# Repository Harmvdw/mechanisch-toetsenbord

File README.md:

# Mechanisch toetsenbord (metaal, split, Lily58-geïnspireerd)

Doel: een split keyboard met aluminium behuizing en plaat, zelf ontworpen in Fusion 360 en zelf gefreesd. Inspiratiebron is de Lily58 (58 toetsen, kolom-stagger).

Deze repo bevat alle werk: referentie-informatie, de PCB-scripts, het behuizingsmodel en de documentatie. Alles wordt hier opgeslagen, zodat het vanaf elke computer bereikbaar is.

## Inhoud

| Bestand | Wat staat erin |
|---|---|
| [docs/eisen-en-wensen.md](docs/eisen-en-wensen.md) | Eisen en wensen van dit project (versie 6) |
| [docs/01-lily58-overzicht.md](docs/01-lily58-overzicht.md) | Layout, varianten, verschillen tussen bronnen |
| [docs/02-onderdelenlijst.md](docs/02-onderdelenlijst.md) | Onderdelenlijsten uit de Lily58 Pro-gids en de blogbouw |
| [docs/03-bouwstappen.md](docs/03-bouwstappen.md) | Bouwvolgorde Lily58 Pro, plus de bouwvolgorde van de blog |
| [docs/04-firmware-qmk.md](docs/04-firmware-qmk.md) | QMK-gegevens, make-commando's, flashen |
| [docs/05-lessen-en-problemen.md](docs/05-lessen-en-problemen.md) | Fouten, oplossingen en tips uit de bronnen |
| [docs/06-naar-metaal.md](docs/06-naar-metaal.md) | Wat uit de bronnen telt voor het metalen ontwerp, en wat nog ontbreekt |
| [docs/07-keebs-vipul-repo.md](docs/07-keebs-vipul-repo.md) | Structuur en inhoud van de keebs-repo (PCB, STL's, firmware) |
| [docs/08-printables-handwired-lily58.md](docs/08-printables-handwired-lily58.md) | Handbedraad Lily58 op Printables: onderdelen, matrix, pinnen, licentie |
| [docs/09-maten-uit-stl-en-gerber.md](docs/09-maten-uit-stl-en-gerber.md) | Gemeten maten: toetsraster, stagger, PCB-rand, plaat en case |
| [docs/10-fusion-opzet.md](docs/10-fusion-opzet.md) | Wat er in het Fusion-document staat: schetsen, parameters, koppelingen |
| [docs/11-pcb-route-en-bestelling.md](docs/11-pcb-route-en-bestelling.md) | PCB-route, wat de Pro-print wel en niet heeft, plan voor de bestelling |
| [docs/12-numpad-en-pcb-route2.md](docs/12-numpad-en-pcb-route2.md) | Numpad (MCP23017, I2C), aangepaste Lily58-print, DRC en Gerbers |
| [docs/13-behuizing.md](docs/13-behuizing.md) | Behuizing prototype v0.1: opbouw, maten, aannames |
| [docs/14-behuizing-fusion.md](docs/14-behuizing-fusion.md) | Behuizing parametrisch in Fusion (beide helften): parameters, controle, open punten |
| [behuizing/](behuizing) | Parametrisch model (CadQuery), STEP/STL-exports, controle-afbeeldingen |
| [pcb/scripts/](pcb/scripts) | Scripts die de numpad-print maken en de Lily58-print aanpassen en routeren |
| [data/lily58-pro-printrand.csv](data/lily58-pro-printrand.csv) | Printrand van de Pro-print (120 punten, mm, zelfde oorsprong als de toetsposities) |
| [data/lily58-pro-switchposities.csv](data/lily58-pro-switchposities.csv) | 29 toetsposities per helft in mm, voor een Fusion-schets |
| [tools/](tools) | Scripts waarmee de maten zijn gemeten (STL en drill-bestanden) |
| [docs/bronnen.md](docs/bronnen.md) | Alle links, met per link wat is gelezen en wat niet |

## Status (16 november 2026)

- **Printen klaar om te bestellen:** `pcb/lily58-pro/Lily58_Pro_gerbers.zip` (met draaiknop, 13 nov) en `pcb/numpad/numpad_gerbers_v0.4.zip` (met draaiknop, 16 nov). Beide door de DRC, zie [docs/12](docs/12-numpad-en-pcb-route2.md).
- **Behuizing:** helften staan parametrisch in Fusion ("Opzet 1-0-0", hub maz1, Admin Project, map Toetsenbord), zie [docs/14](docs/14-behuizing-fusion.md). De numpad (bak, plaat, draaiknop) is op 16 nov in hetzelfde document opgebouwd met `behuizing/fusion/opbouw_numpad.py`; opgeslagen als "Opzet 1-0-1" (hub testteam, Intern/Harm). STEP-modellen van onderdelen: `behuizing/step/BRONNEN.md`.
- Connector (magnetisch): levering januari; daarna `conn_diepte` opmeten.

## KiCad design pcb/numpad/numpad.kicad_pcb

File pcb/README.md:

# Printen (KiCad 10)

| Map | Inhoud |
|---|---|
| `lily58-pro/` | Aangepaste Lily58 Pro-print (route 2): `Lily58_Pro.kicad_pcb` + `.kicad_pro`, eigen footprintbibliotheek, laatste DRC-rapport, **Gerbers voor de bestelling** (`Lily58_Pro_gerbers.zip`, 13 nov, met draaiknop). `Lily58_Pro_uit_gerbers.step`: de print als 3D-model, gemaakt uit die Gerbers (printrand × 1,6 mm met alle gaten en sleuven), in het master-assenstelsel van de behuizing (print op z 7,5–9,1 mm). |
| `lily58-pro/origineel/` | Uitgangspunt: Lily58 Pro van kata0510 (KiCad 5-schema, netlijst) en het bord zoals het in KiCad 10 werd geopend, plus het eerste DRC-rapport (1093 meldingen). |
| `numpad/` | Numpad-print v0.4 met draaiknop (gegenereerd door `scripts/gen_numpad.py`), DRC-rapport `numpad_DRC.rpt` en **Gerbers voor de bestelling** (`numpad_gerbers_v0.4.zip`, 16 nov). De zip van v0.3 (zonder draaiknop) niet meer bestellen. |
| `scripts/` | Scripts die de numpad-print maken en de Lily58-print aanpassen en routeren; `gerber_naar_step.py` maakt een STEP uit Gerbers. |

STEP opnieuw maken (Lily58-helft, master-assenstelsel):

```
python3 pcb/scripts/gerber_naar_step.py pcb/lily58-pro/Lily58_Pro_gerbers.zip pcb/lily58-pro/Lily58_Pro_uit_gerbers.step --dx -158.6 --dy 46.21 --z0 7.5
```

Met `--koper` komen de koperlagen erbij; het bestand wordt dan ca. 140 MB.

Uitleg en DRC-resultaten: [docs/12-numpad-en-pcb-route2.md](../docs/12-numpad-en-pcb-route2.md).

Openen in KiCad: de footprintbibliotheek `Lily58_Pro-footprint.pretty` staat naast het bord, maar is in KiCad niet als bibliotheek geregistreerd (DRC meldt `lib_footprint_issues`). Voor het bord zelf is dat niet nodig.

Licentie Lily58: MIT (kata0510).

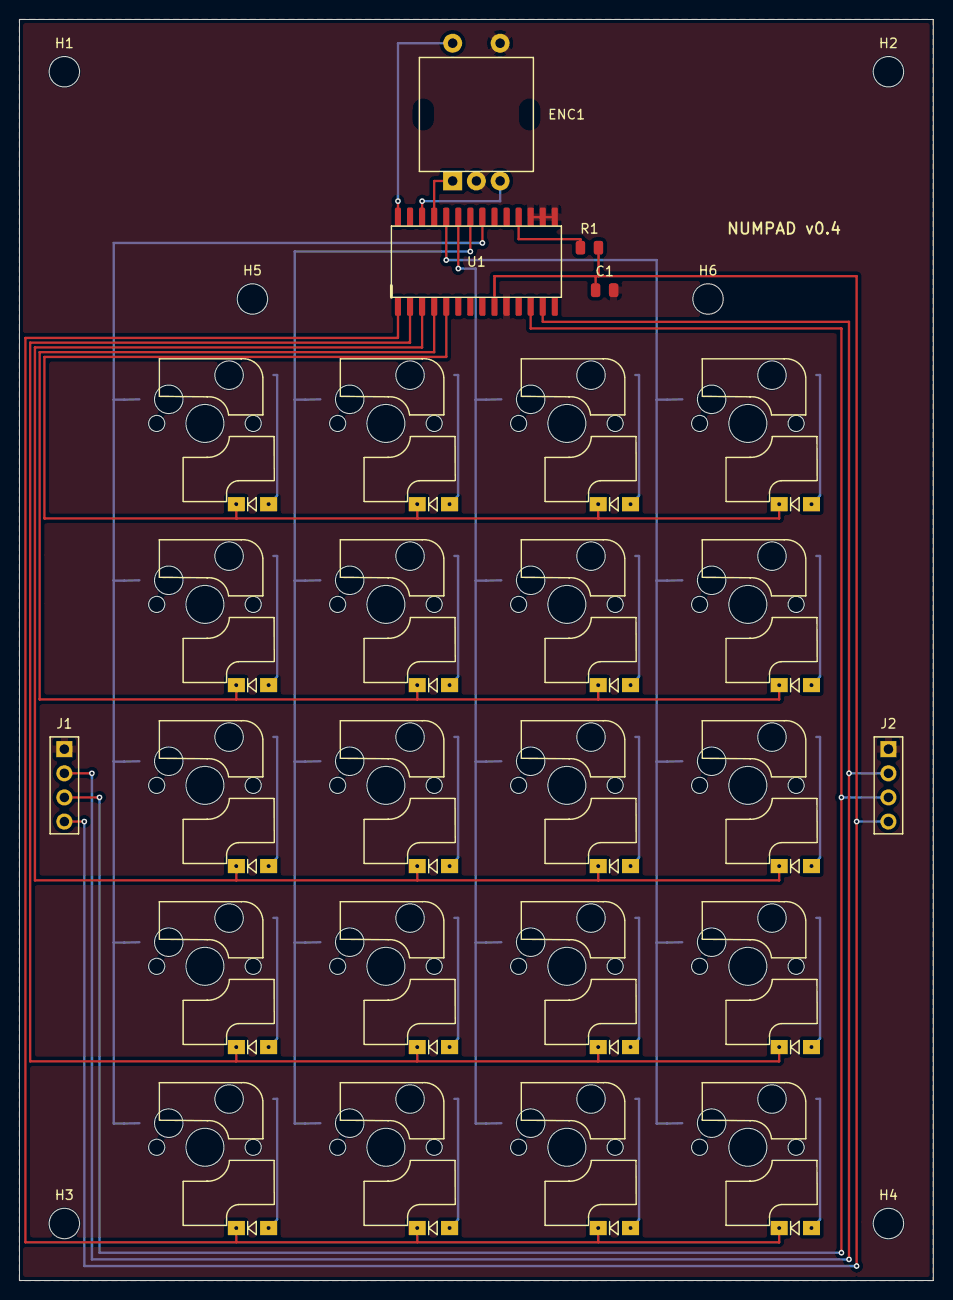
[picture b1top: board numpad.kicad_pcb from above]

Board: 2 copper layers, 96.2 x 132.8 mm, 52 parts (0 on the bottom side), 37 nets.

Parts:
C1: 100nF; C_0805
D1, D2, D3, D4, D5, D6, D7, D8, D9, D10, D11, D12, D13, D14, D15, D16, D17, D18, D19, D20: 1N4148W; Diode_SOD123
ENC1: EC11 met drukknop; RotaryEncoder_EC11E_Switch
H1, H2, H3, H4, H5, H6: M3; MountingHole_3.2mm
J1, J2: Adafruit 5358; Magnetic_5358_1x4_P2.54_Vertical
R1: 10k; R_0805
SW1, SW2, SW3, SW4, SW5, SW6, SW7, SW8, SW9, SW10, SW11, SW12, SW13, SW14, SW15, SW16, SW17, SW18, SW19, SW20: MX_hotswap; CherryMX_KailhLowProfile_Hotswap_edge
U1: MCP23017-E/SO; SOIC-28W_7.5x17.9mm_P1.27mm

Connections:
GND: C1.2, ENC1.C, ENC1.S2, J1.1, J2.1, U1.10, U1.15, U1.16, U1.17
unnamed: D1.2, SW1.2
unnamed: D2.2, SW2.2
unnamed: D3.2, SW3.2
unnamed: D4.2, SW4.2
unnamed: D5.2, SW5.2
unnamed: D6.2, SW6.2
unnamed: D7.2, SW7.2
unnamed: D8.2, SW8.2
unnamed: D9.2, SW9.2
unnamed: D10.2, SW10.2
unnamed: D11.2, SW11.2
unnamed: D12.2, SW12.2
unnamed: D13.2, SW13.2
unnamed: D14.2, SW14.2
unnamed: D15.2, SW15.2
unnamed: D16.2, SW16.2
unnamed: D17.2, SW17.2
unnamed: D18.2, SW18.2
unnamed: D19.2, SW19.2
unnamed: D20.2, SW20.2
SCL: J1.3, J2.3, U1.12
SDA: J1.2, J2.2, U1.13
VCC: C1.1, J1.4, J2.4, R1.2, U1.9
nRESET: R1.1, U1.18
np_col0: SW1.1, SW5.1, SW9.1, SW13.1, SW17.1, U1.21
np_col1: SW2.1, SW6.1, SW10.1, SW14.1, SW18.1, U1.22
np_col2: SW3.1, SW7.1, SW11.1, SW15.1, SW19.1, U1.23
np_col3: SW4.1, SW8.1, SW12.1, SW16.1, SW20.1, U1.24
np_encA: ENC1.A, U1.25
np_encB: ENC1.B, U1.26
np_encS: ENC1.S1, U1.28
np_row0: D1.1, D2.1, D3.1, D4.1, U1.5
np_row1: D5.1, D6.1, D7.1, D8.1, U1.4
np_row2: D9.1, D10.1, D11.1, D12.1, U1.3
np_row3: D13.1, D14.1, D15.1, D16.1, U1.2
np_row4: D17.1, D18.1, D19.1, D20.1, U1.1
